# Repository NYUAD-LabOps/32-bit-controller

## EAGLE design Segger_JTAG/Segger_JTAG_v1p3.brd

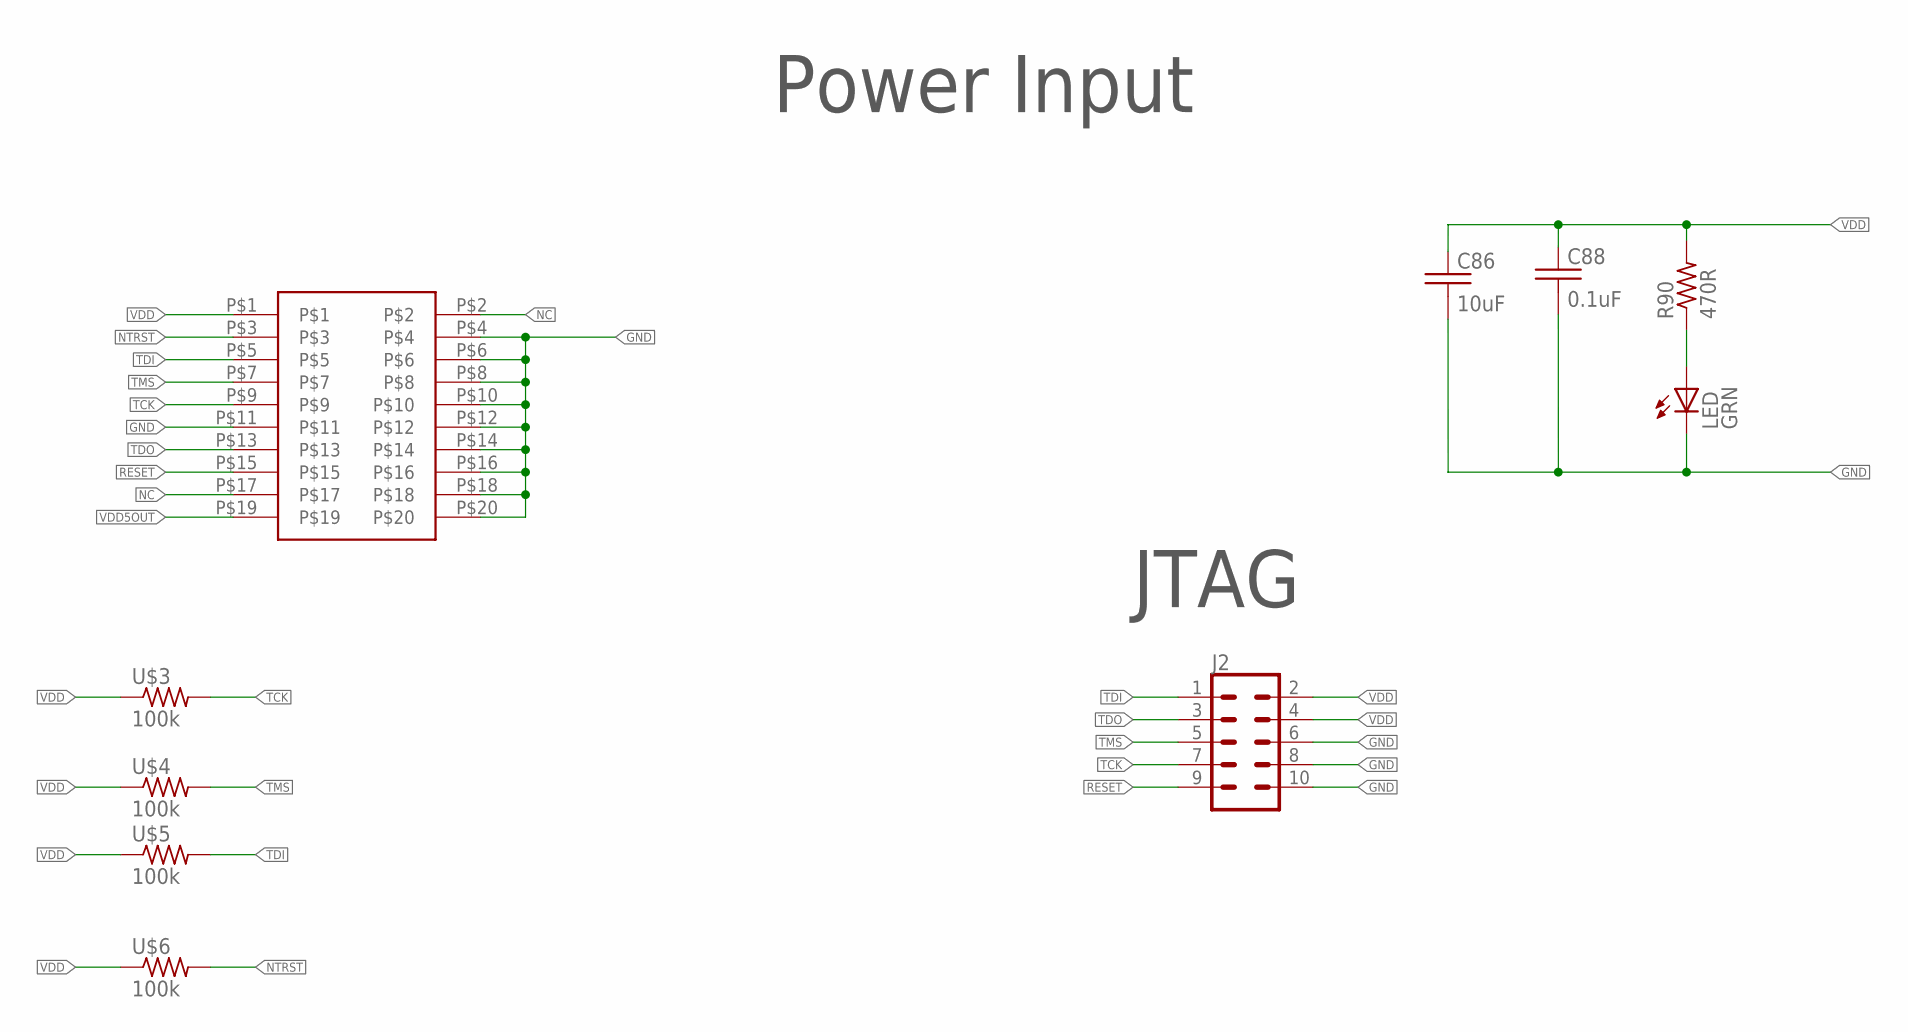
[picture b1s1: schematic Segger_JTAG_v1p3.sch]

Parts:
C86: 10uF; 0805
C88: 0.1uF; 0805
J2: CONN_05X2PTH; 2X5
LED: LED_0805_GREEN
R90: 470R; 0805
U$2: 2_X_10_HEADER_GENERIC; 2_X_10_.1_INCH
U$3, U$4, U$5, U$6: 100k; 0805

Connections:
GND: C86.2, C88.2, J2.6, J2.8, J2.10, LED.C, U$2.P$4, U$2.P$6, U$2.P$8, U$2.P$10, U$2.P$11, U$2.P$12, U$2.P$14, U$2.P$16, U$2.P$18, U$2.P$20
unnamed: LED.A, R90.1
NC: U$2.P$2, U$2.P$17
NTRST: U$2.P$3, U$6.2
RESET: J2.9, U$2.P$15
TCK: J2.7, U$2.P$9, U$3.2
TDI: J2.1, U$2.P$5, U$5.2
TDO: J2.3, U$2.P$13
TMS: J2.5, U$2.P$7, U$4.2
VDD: C86.1, C88.1, J2.2, J2.4, R90.2, U$2.P$1, U$3.1, U$4.1, U$5.1, U$6.1
VDD5OUT: U$2.P$19

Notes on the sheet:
Power Input
JTAG

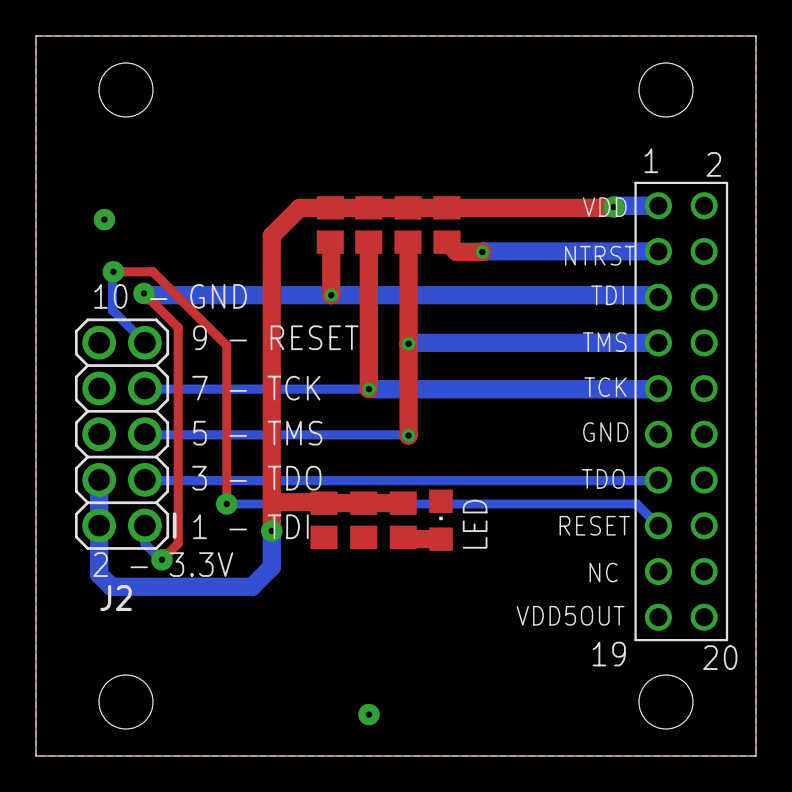
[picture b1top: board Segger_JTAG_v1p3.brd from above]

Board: 2 copper layers, 40.0 x 40.0 mm, 10 parts (0 on the bottom side), 10 nets.

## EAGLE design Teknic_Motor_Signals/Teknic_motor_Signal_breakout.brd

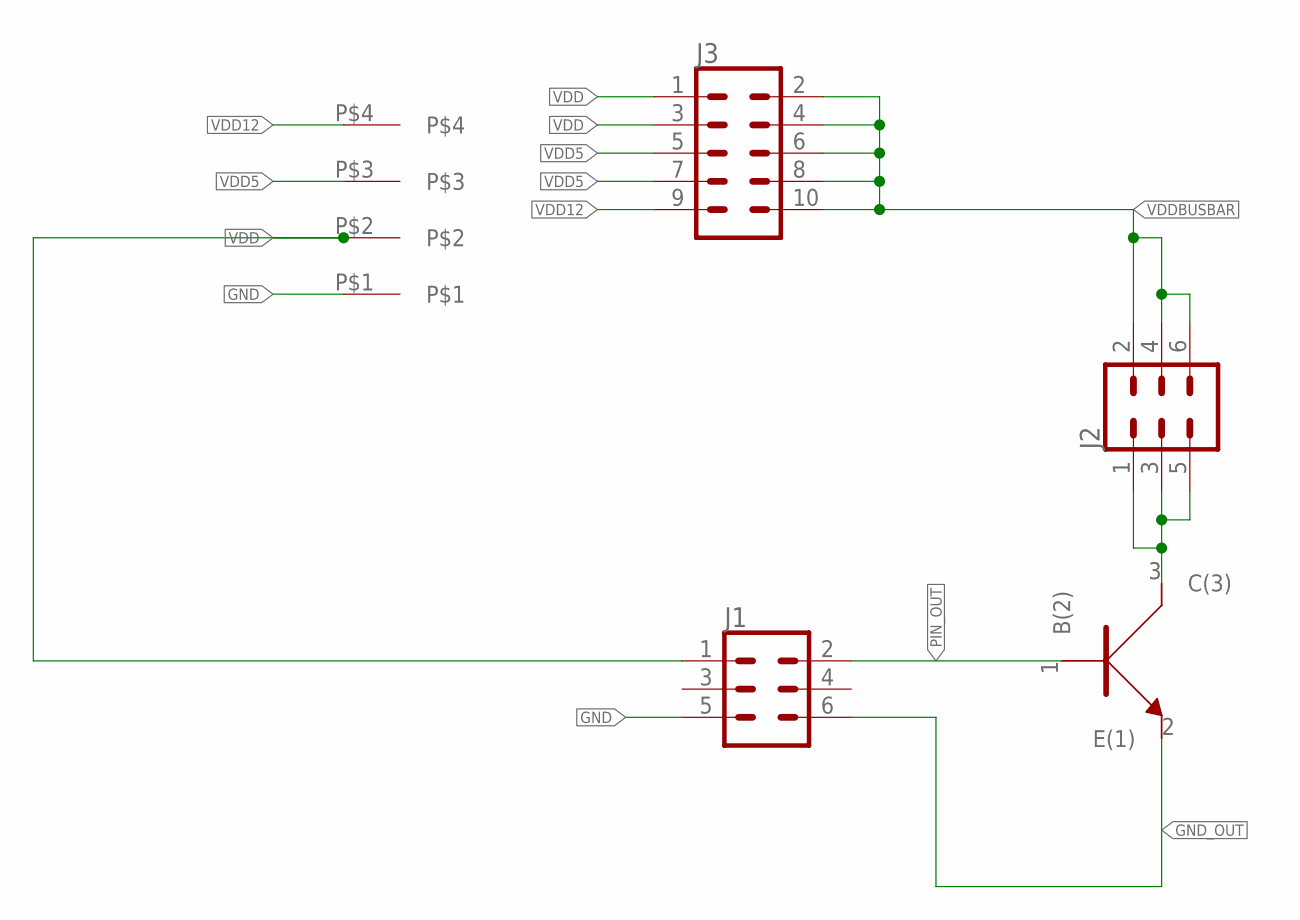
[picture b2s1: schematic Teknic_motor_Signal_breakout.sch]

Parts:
J1, J2: CONN_03X2; 2X3
J3: CONN_05X2PTH; 2X5
J5: 4-pos; 1X4_3.81MM_PITCH
U1: NPN; SOT323

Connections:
GND: J1.5, J5.P$1
GND_OUT: J1.6, U1.2 (E(1))
unnamed: J2.1, J2.3, J2.5, U1.3 (C(3))
PIN_OUT: J1.2, U1.1 (B(2))
VDD: J1.1, J3.1, J3.3, J5.P$2
VDD5: J3.5, J3.7, J5.P$3
VDD12: J3.9, J5.P$4
VDDBUSBAR: J2.2, J2.4, J2.6, J3.2, J3.4, J3.6, J3.8, J3.10

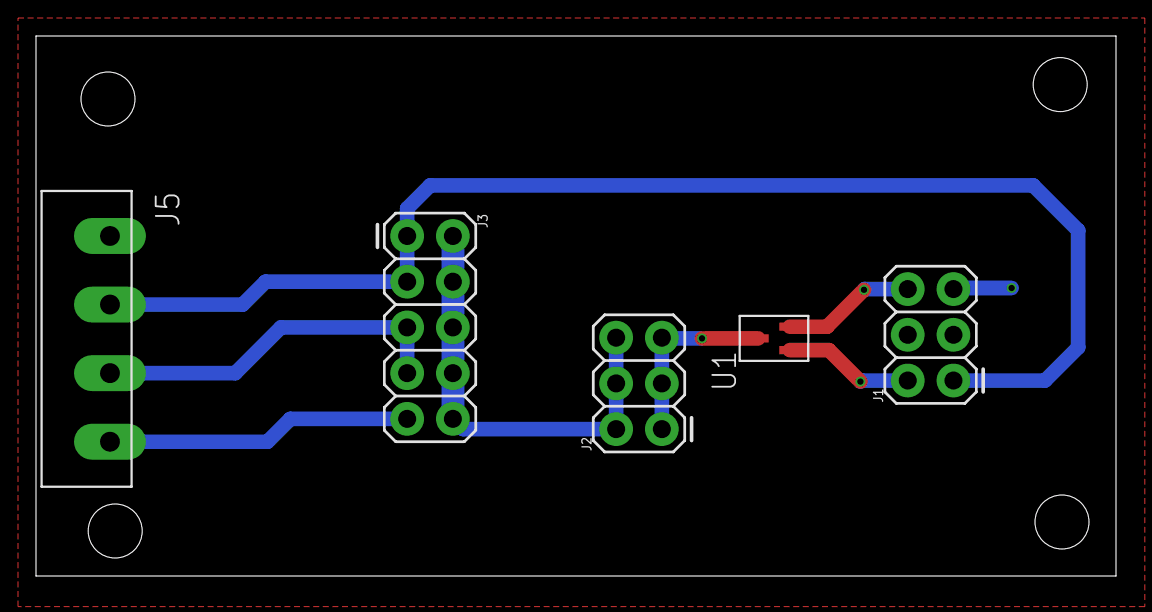
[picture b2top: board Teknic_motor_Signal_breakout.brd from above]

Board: 2 copper layers, 60.0 x 30.0 mm, 5 parts (0 on the bottom side), 8 nets.

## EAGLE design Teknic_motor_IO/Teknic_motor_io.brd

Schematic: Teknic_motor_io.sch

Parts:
J1, J2, J3, J4, J7, J9, J10, J11, J12: TEKNIC_8PIN_MOTOR; CON_39281083
J5: 2-pos; 2_3.81MM_PITCH
J8: 40-pos; HEADER_2_X_20_.1_INCH
R3, R7, R8, R10, R11, R21, R22, R24, R25, R29, R30, R32, R33, R37, R38, R40, R41, R45, R46, R48, R49, R53, R54, R56, R57, R61, R62, R64, R65, R69, R70, R72, R73, R77, R78, R80: 1K0; 0402
R4, R5, R6, R9, R12, R19, R20, R23, R26, R27, R28, R31, R34, R35, R36, R39, R42, R43, R44, R47, R50, R51, R52, R55, R58, R59, R60, R63, R66, R67, R68, R71, R74, R75, R76, R79: 33R0; 0402
U2, U3, U4, U5, U6, U10, U11, U12, U13, U14, U15, U16, U17, U18, U19, U20, U21, U22, U23, U24, U25, U26, U27, U28, U29, U30, U31, U32, U33, U34, U35, U36, U37, U38, U39, U40: NPN; SOT323

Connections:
GND: J5.P$1, J8.P$37, J8.P$38, J8.P$39, J8.P$40, U2.2 (E(1)), U3.2 (E(1)), U4.2 (E(1)), U5.2 (E(1)), U6.2 (E(1)), U10.2 (E(1)), U11.2 (E(1)), U12.2 (E(1)), U13.2 (E(1)), U14.2 (E(1)), U15.2 (E(1)), U16.2 (E(1)), U17.2 (E(1)), U18.2 (E(1)), U19.2 (E(1)), U20.2 (E(1)), U21.2 (E(1)), U22.2 (E(1)), U23.2 (E(1)), U24.2 (E(1)), U25.2 (E(1)), U26.2 (E(1)), U27.2 (E(1)), U28.2 (E(1)), U29.2 (E(1)), U30.2 (E(1)), U31.2 (E(1)), U32.2 (E(1)), U33.2 (E(1)), U34.2 (E(1)), U35.2 (E(1)), U36.2 (E(1)), U37.2 (E(1)), U38.2 (E(1)), U39.2 (E(1)), U40.2 (E(1))
M1_DIR: J8.P$2, R5.P$1 (1)
M1_ENABLE: J8.P$3, R6.P$1 (1)
M1_HLFB: R9.P$1 (1)
M1_STEP: J8.P$1, R4.P$1 (1)
M2_DIR: J8.P$5, R19.P$1 (1)
M2_ENABLE: J8.P$6, R20.P$1 (1)
M2_HLFB: R23.P$1 (1)
M2_STEP: J8.P$4, R12.P$1 (1)
M3_DIR: J8.P$8, R27.P$1 (1)
M3_ENABLE: J8.P$9, R28.P$1 (1)
M3_HLFB: R31.P$1 (1)
M3_STEP: J8.P$7, R26.P$1 (1)
M4_DIR: J8.P$11, R35.P$1 (1)
M4_ENABLE: J8.P$12, R36.P$1 (1)
M4_HLFB: R39.P$1 (1)
M4_STEP: J8.P$10, R34.P$1 (1)
M5_DIR: J8.P$14, R43.P$1 (1)
M5_ENABLE: J8.P$15, R44.P$1 (1)
M5_HLFB: R47.P$1 (1)
M5_STEP: J8.P$13, R42.P$1 (1)
M6_DIR: J8.P$17, R51.P$1 (1)
M6_ENABLE: J8.P$18, R52.P$1 (1)
M6_HLFB: R55.P$1 (1)
M6_STEP: J8.P$16, R50.P$1 (1)
M7_DIR: J8.P$20, R59.P$1 (1)
M7_ENABLE: J8.P$21, R60.P$1 (1)
M7_HLFB: R63.P$1 (1)
M7_STEP: J8.P$19, R58.P$1 (1)
M8_DIR: J8.P$23, R67.P$1 (1)
M8_ENABLE: J8.P$24, R68.P$1 (1)
M8_HLFB: R71.P$1 (1)
M8_STEP: J8.P$22, R66.P$1 (1)
M9_DIR: J8.P$26, R75.P$1 (1)
M9_ENABLE: J8.P$27, R76.P$1 (1)
M9_HLFB: R79.P$1 (1)
M9_STEP: J8.P$25, R74.P$1 (1)
M10_DIR: J8.P$29
M10_ENABLE: J8.P$30
M10_STEP: J8.P$28
M11_DIR: J8.P$32
M11_ENABLE: J8.P$33
M11_STEP: J8.P$31
M12_DIR: J8.P$35
M12_ENABLE: J8.P$36
M12_STEP: J8.P$34
MR_DIR: J1.7 (7-INPUT_A-), J2.7 (7-INPUT_A-), J3.7 (7-INPUT_A-), J4.7 (7-INPUT_A-), J7.7 (7-INPUT_A-), J9.7 (7-INPUT_A-), J10.7 (7-INPUT_A-), J11.7 (7-INPUT_A-), J12.7 (7-INPUT_A-), R7.P$1 (1), R21.P$1 (1), R29.P$1 (1), R37.P$1 (1), R45.P$1 (1), R53.P$1 (1), R61.P$1 (1), R69.P$1 (1), R77.P$1 (1), U3.3 (C(3)), U10.3 (C(3)), U14.3 (C(3)), U18.3 (C(3)), U22.3 (C(3)), U26.3 (C(3)), U30.3 (C(3)), U34.3 (C(3)), U38.3 (C(3))
MR_ENABLE: J1.8 (8-ENABLE-), J2.8 (8-ENABLE-), J3.8 (8-ENABLE-), J4.8 (8-ENABLE-), J7.8 (8-ENABLE-), J9.8 (8-ENABLE-), J10.8 (8-ENABLE-), J11.8 (8-ENABLE-), J12.8 (8-ENABLE-), R8.P$1 (1), R22.P$1 (1), R30.P$1 (1), R38.P$1 (1), R46.P$1 (1), R54.P$1 (1), R62.P$1 (1), R70.P$1 (1), R78.P$1 (1), U4.3 (C(3)), U11.3 (C(3)), U15.3 (C(3)), U19.3 (C(3)), U23.3 (C(3)), U27.3 (C(3)), U31.3 (C(3)), U35.3 (C(3)), U39.3 (C(3))
MR_HLFB: J1.5 (5-HLFB-), J2.5 (5-HLFB-), J3.5 (5-HLFB-), J4.5 (5-HLFB-), J7.5 (5-HLFB-), J9.5 (5-HLFB-), J10.5 (5-HLFB-), J11.5 (5-HLFB-), J12.5 (5-HLFB-), R10.P$1 (1), R24.P$1 (1), R32.P$1 (1), R40.P$1 (1), R48.P$1 (1), R56.P$1 (1), R64.P$1 (1), R72.P$1 (1), R80.P$1 (1), U5.3 (C(3)), U12.3 (C(3)), U16.3 (C(3)), U20.3 (C(3)), U24.3 (C(3)), U28.3 (C(3)), U32.3 (C(3)), U36.3 (C(3)), U40.3 (C(3))
MR_STEP: J1.6 (6-INPUT_B-), J2.6 (6-INPUT_B-), J3.6 (6-INPUT_B-), J4.6 (6-INPUT_B-), J7.6 (6-INPUT_B-), J9.6 (6-INPUT_B-), J10.6 (6-INPUT_B-), J11.6 (6-INPUT_B-), J12.6 (6-INPUT_B-), R3.P$1 (1), R11.P$1 (1), R25.P$1 (1), R33.P$1 (1), R41.P$1 (1), R49.P$1 (1), R57.P$1 (1), R65.P$1 (1), R73.P$1 (1), U2.3 (C(3)), U6.3 (C(3)), U13.3 (C(3)), U17.3 (C(3)), U21.3 (C(3)), U25.3 (C(3)), U29.3 (C(3)), U33.3 (C(3)), U37.3 (C(3))
unnamed: R5.P$2 (2), U3.1 (B(2))
unnamed: R6.P$2 (2), U4.1 (B(2))
unnamed: R4.P$2 (2), U2.1 (B(2))
unnamed: R9.P$2 (2), U5.1 (B(2))
unnamed: R19.P$2 (2), U10.1 (B(2))
unnamed: R20.P$2 (2), U11.1 (B(2))
unnamed: R12.P$2 (2), U6.1 (B(2))
unnamed: R23.P$2 (2), U12.1 (B(2))
unnamed: R27.P$2 (2), U14.1 (B(2))
unnamed: R28.P$2 (2), U15.1 (B(2))
unnamed: R26.P$2 (2), U13.1 (B(2))
unnamed: R31.P$2 (2), U16.1 (B(2))
unnamed: R35.P$2 (2), U18.1 (B(2))
unnamed: R36.P$2 (2), U19.1 (B(2))
unnamed: R34.P$2 (2), U17.1 (B(2))
unnamed: R39.P$2 (2), U20.1 (B(2))
unnamed: R43.P$2 (2), U22.1 (B(2))
unnamed: R44.P$2 (2), U23.1 (B(2))
unnamed: R42.P$2 (2), U21.1 (B(2))
unnamed: R47.P$2 (2), U24.1 (B(2))
unnamed: R51.P$2 (2), U26.1 (B(2))
unnamed: R52.P$2 (2), U27.1 (B(2))
unnamed: R50.P$2 (2), U25.1 (B(2))
unnamed: R55.P$2 (2), U28.1 (B(2))
unnamed: R59.P$2 (2), U30.1 (B(2))
unnamed: R60.P$2 (2), U31.1 (B(2))
unnamed: R58.P$2 (2), U29.1 (B(2))
unnamed: R63.P$2 (2), U32.1 (B(2))
unnamed: R67.P$2 (2), U34.1 (B(2))
unnamed: R68.P$2 (2), U35.1 (B(2))
unnamed: R66.P$2 (2), U33.1 (B(2))
unnamed: R71.P$2 (2), U36.1 (B(2))
unnamed: R75.P$2 (2), U38.1 (B(2))
unnamed: R76.P$2 (2), U39.1 (B(2))
unnamed: R74.P$2 (2), U37.1 (B(2))
unnamed: R79.P$2 (2), U40.1 (B(2))
VDD12: J1.1 (1-HLFB+), J1.2 (2-INPUT_B+), J1.3 (3-INPUT_A+), J1.4 (4-ENABLE+), J2.1 (1-HLFB+), J2.2 (2-INPUT_B+), J2.3 (3-INPUT_A+), J2.4 (4-ENABLE+), J3.1 (1-HLFB+), J3.2 (2-INPUT_B+), J3.3 (3-INPUT_A+), J3.4 (4-ENABLE+), J4.1 (1-HLFB+), J4.2 (2-INPUT_B+), J4.3 (3-INPUT_A+), J4.4 (4-ENABLE+), J5.P$2, J7.1 (1-HLFB+), J7.2 (2-INPUT_B+), J7.3 (3-INPUT_A+), J7.4 (4-ENABLE+), J9.1 (1-HLFB+), J9.2 (2-INPUT_B+), J9.3 (3-INPUT_A+), J9.4 (4-ENABLE+), J10.1 (1-HLFB+), J10.2 (2-INPUT_B+), J10.3 (3-INPUT_A+), J10.4 (4-ENABLE+), J11.1 (1-HLFB+), J11.2 (2-INPUT_B+), J11.3 (3-INPUT_A+), J11.4 (4-ENABLE+), J12.1 (1-HLFB+), J12.2 (2-INPUT_B+), J12.3 (3-INPUT_A+), J12.4 (4-ENABLE+), R3.P$2 (2), R7.P$2 (2), R8.P$2 (2), R10.P$2 (2), R11.P$2 (2), R21.P$2 (2), R22.P$2 (2), R24.P$2 (2), R25.P$2 (2), R29.P$2 (2), R30.P$2 (2), R32.P$2 (2), R33.P$2 (2), R37.P$2 (2), R38.P$2 (2), R40.P$2 (2), R41.P$2 (2), R45.P$2 (2), R46.P$2 (2), R48.P$2 (2), R49.P$2 (2), R53.P$2 (2), R54.P$2 (2), R56.P$2 (2), R57.P$2 (2), R61.P$2 (2), R62.P$2 (2), R64.P$2 (2), R65.P$2 (2), R69.P$2 (2), R70.P$2 (2), R72.P$2 (2), R73.P$2 (2), R77.P$2 (2), R78.P$2 (2), R80.P$2 (2)

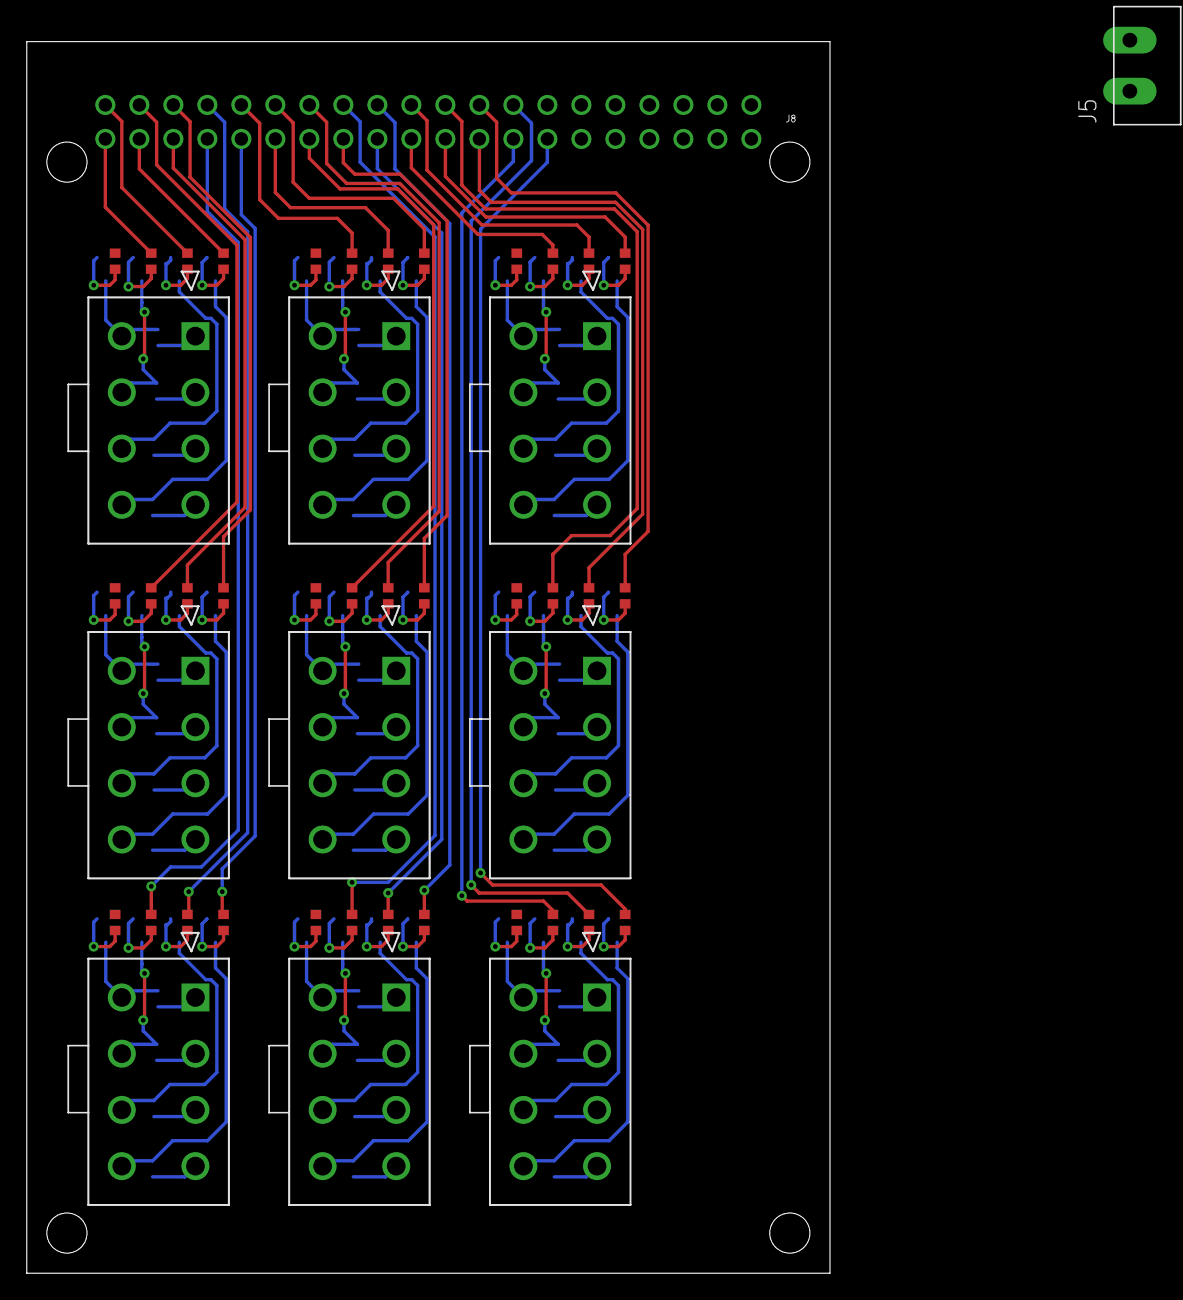
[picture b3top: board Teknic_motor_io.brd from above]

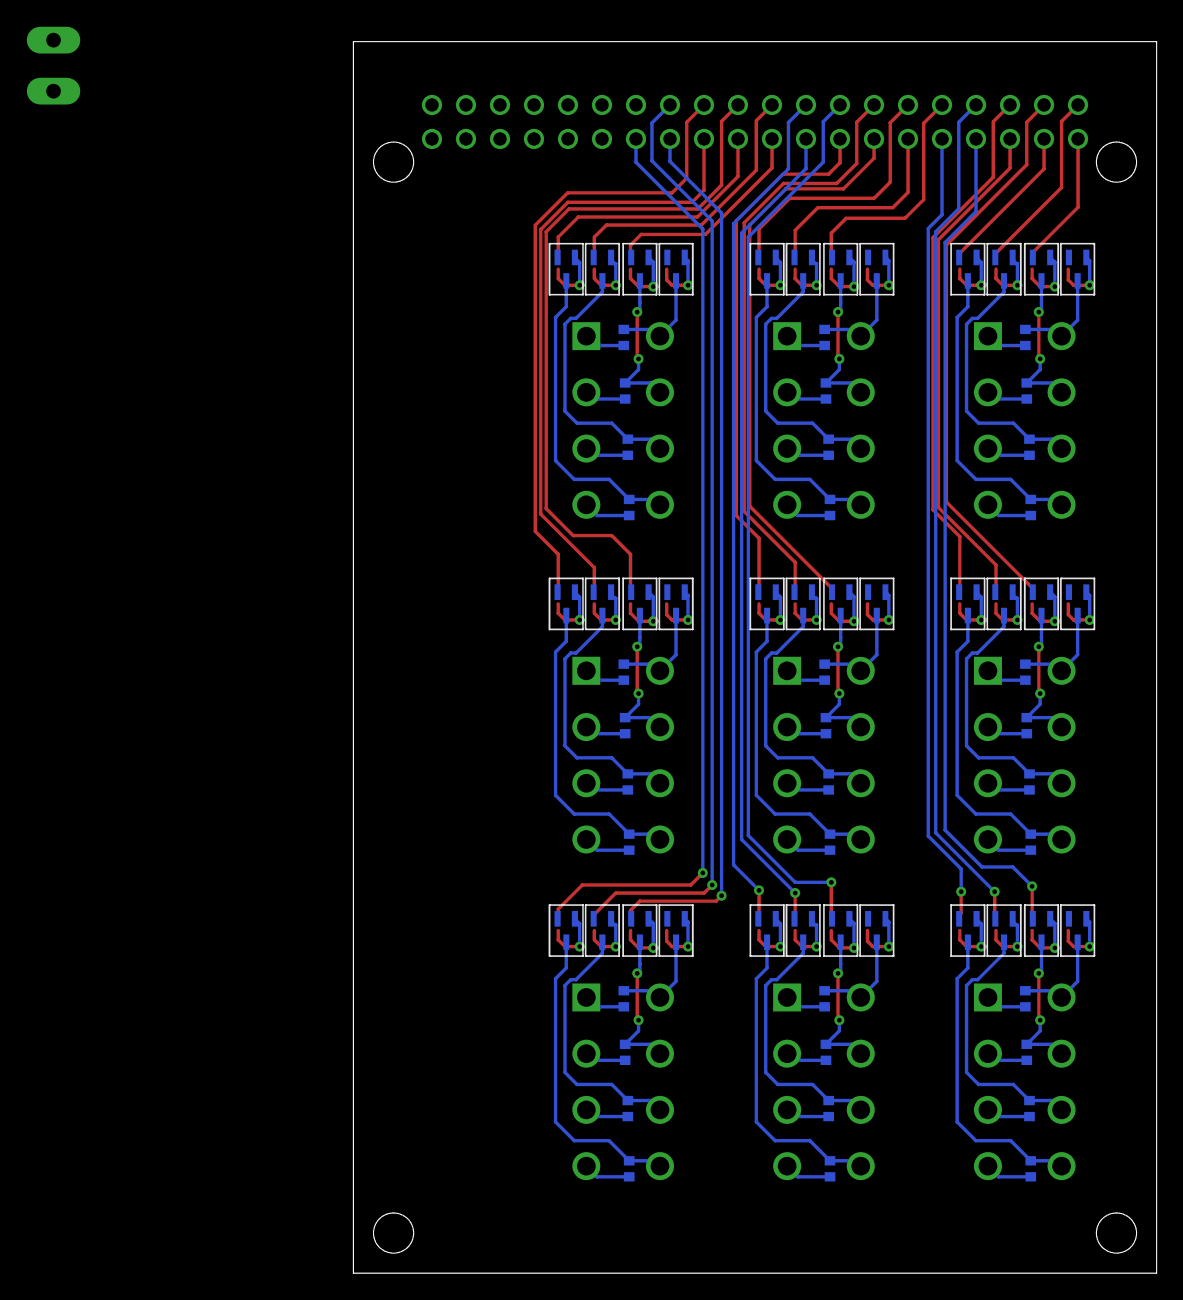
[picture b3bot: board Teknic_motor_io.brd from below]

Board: 2 copper layers, 60.0 x 92.0 mm, 119 parts (72 on the bottom side), 69 nets.

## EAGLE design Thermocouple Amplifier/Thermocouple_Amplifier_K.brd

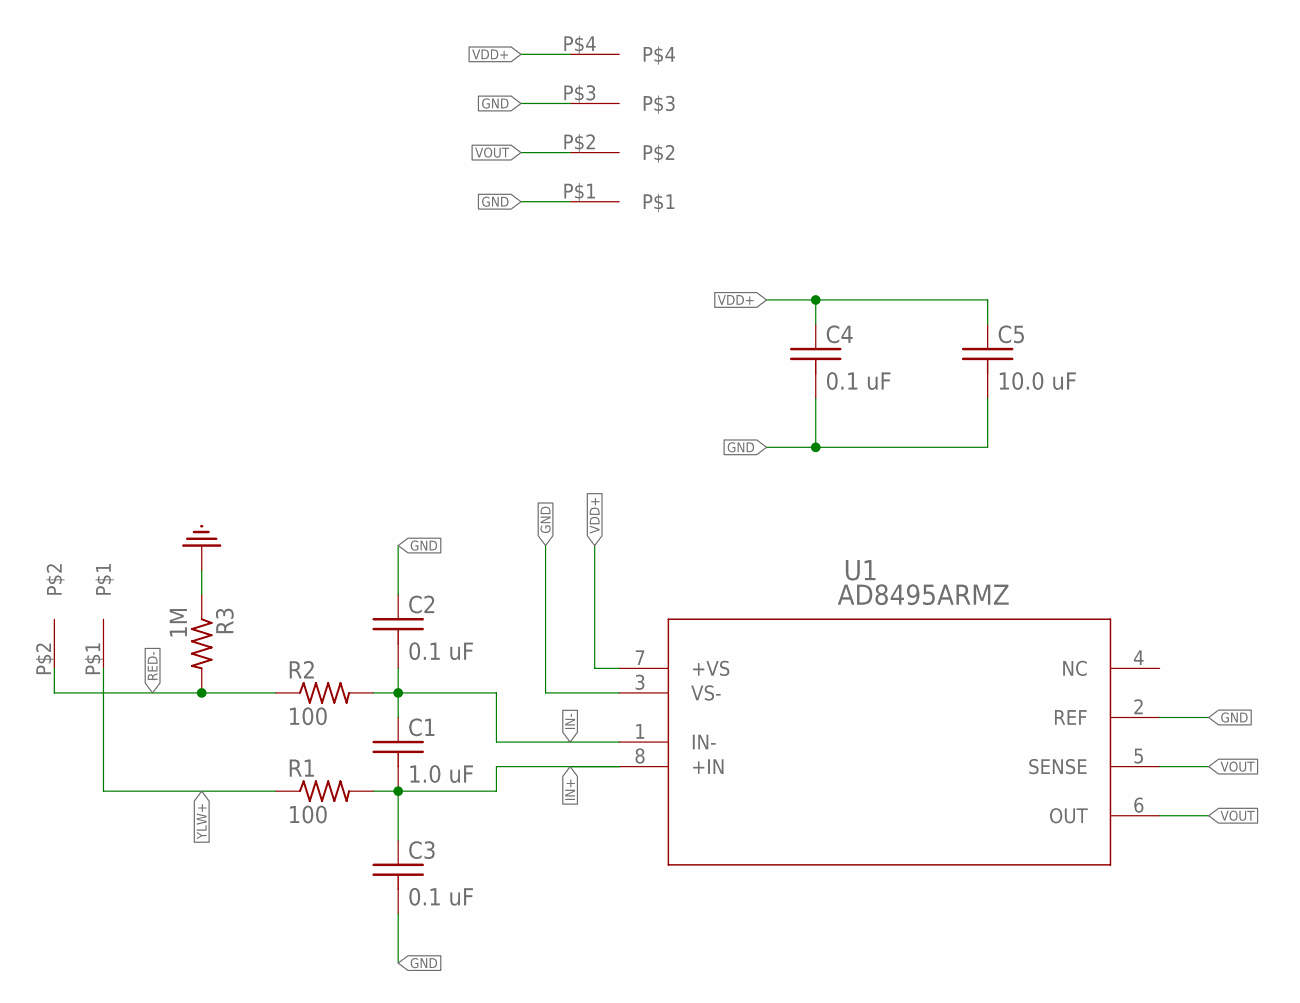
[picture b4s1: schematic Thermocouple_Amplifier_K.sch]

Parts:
C1: 1.0 uF; 0402
C2, C3, C4: 0.1 uF; 0402
C5: 10.0 uF; 0402
J1: 3.81MM_1_X_2_RT_ANGLE_PLUG_HEADER; 2_3.81MM_PITCH
J2: 3.81MM_1_X_4_RT_ANGLE_PLUG_HEADER; 1X4_3.81MM_PITCH
R1, R2: 100; 0402
R3: 1M; 0402
U1: AD8495ARMZ; RM_8_ADI

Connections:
GND: C2.P$1 (1), C3.P$2 (2), C4.P$2 (2), C5.P$2 (2), J2.P$1, J2.P$3, R3.P$1 (1), U1.2 (REF), U1.3 (VS-)
IN+: C1.P$2 (2), C3.P$1 (1), R1.P$2 (2), U1.8 (+IN)
IN-: C1.P$1 (1), C2.P$2 (2), R2.P$2 (2), U1.1 (IN-)
RED-: J1.P$2, R2.P$1 (1), R3.P$2 (2)
VDD+: C4.P$1 (1), C5.P$1 (1), J2.P$4, U1.7 (+VS)
VOUT: J2.P$2, U1.5 (SENSE), U1.6 (OUT)
YLW+: J1.P$1, R1.P$1 (1)

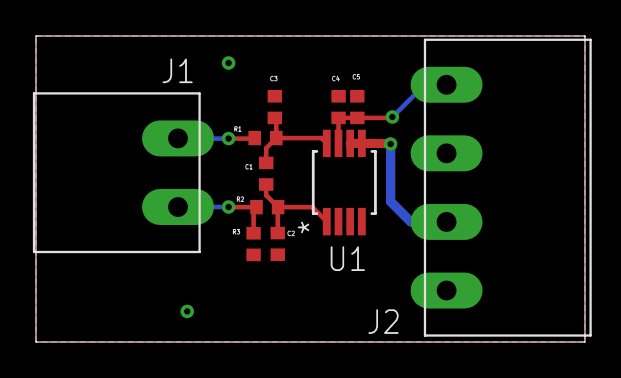
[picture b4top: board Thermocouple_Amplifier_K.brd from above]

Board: 2 copper layers, 30.5 x 17.0 mm, 11 parts (0 on the bottom side), 7 nets.

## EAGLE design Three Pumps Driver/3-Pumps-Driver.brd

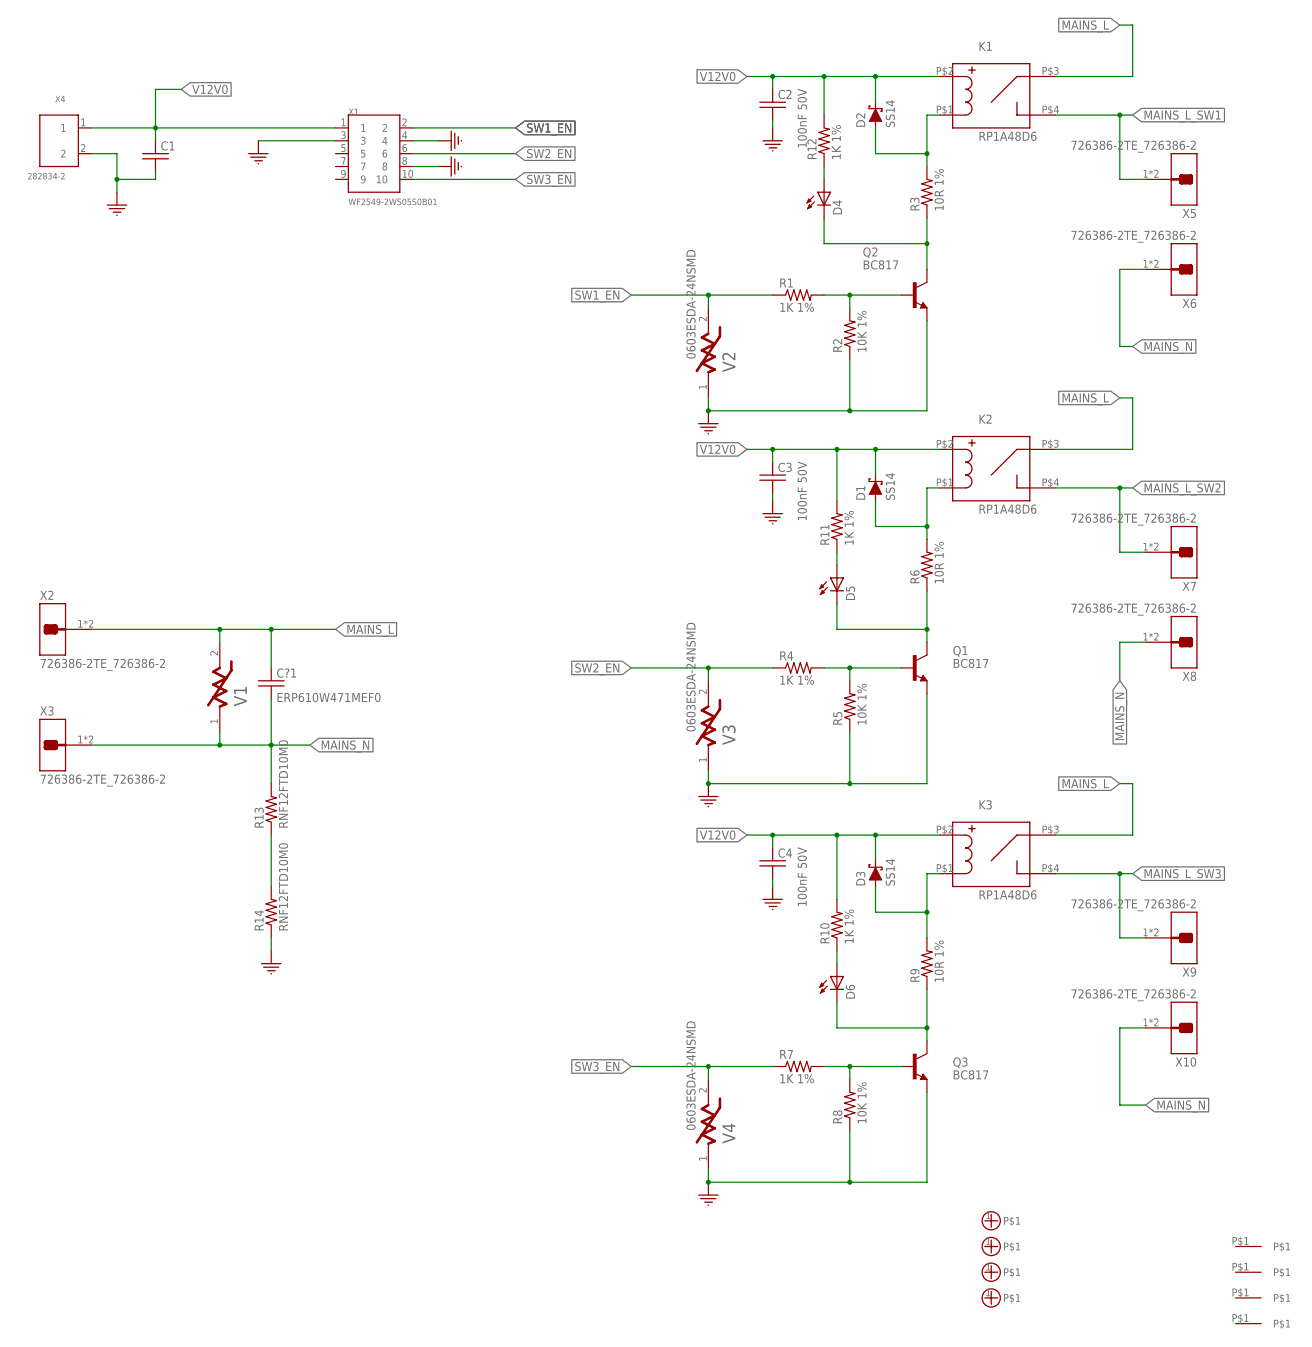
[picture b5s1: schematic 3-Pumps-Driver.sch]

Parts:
C1: C_0603EIA0603; EIA0603
C2, C3, C4: 100nF 50V; EIA0603
C?1: ERP610W471MEF0; CAPACITOR-FILM-RM12.5MM-12MM
D1, D2, D3: SS14; SMA
D4, D5, D6: 26-21/GPC-F3138B/CA; SMD1206-LED
FID1, FID2, FID3, FID4: FIDUCIAL
K1, K2, K3: RP1A48D6; SSR_RP1A
M1, M2, M3, M4: M_HOLE_3M; PCB_SCREW_M3_POWER
Q1, Q2, Q3: BC817; SOT23
R1, R4, R7: 1K 1%; EIA0603
R2, R5, R8: 10K 1%; EIA0603
R3, R6, R9: 10R 1%; EIA1206
R10, R11, R12: 1K 1%; EIA1206
R13, R14: RNF12FTD10M0; RES-RM12.5-VR37
V1: B72205S0271K101B72205S2131K101; EPCOS_B72205S0271K101_0
V2, V3, V4: 0603ESDA-24NSMD; EIA0603
X1: WF2549-2WS05S0B01; X10_100MIL_2XROW_VERT
X2, X3, X5, X6, X7, X8, X9, X10: 726386-2TE_726386-2; TE_726386-2
X4: 282834-2; TE_282834-2_0

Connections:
GND: C1.2, C2.2, C3.2, C4.2, Q1.2 (E), Q2.2 (E), Q3.2 (E), R2.1, R5.1, R8.1, R14.1, V2.1, V3.1, V4.1, X1.3, X1.4, X1.8, X4.2
MAINS_L: C?1.1, K1.P$3 (3), K2.P$3 (3), K3.P$3 (3), V1.2, X2.1, X2.1-2
MAINS_L_SW1: K1.P$4 (4), X5.1, X5.1-2
MAINS_L_SW2: K2.P$4 (4), X7.1, X7.1-2
MAINS_L_SW3: K3.P$4 (4), X9.1, X9.1-2
MAINS_N: C?1.2, R13.2, V1.1, X3.1, X3.1-2, X6.1, X6.1-2, X8.1, X8.1-2, X10.1, X10.1-2
unnamed: D4.1 (A), R12.1
unnamed: Q2.1 (B), R1.2, R2.2
unnamed: Q1.1 (B), R4.2, R5.2
unnamed: D2.2 (A), K1.P$1 (1), R3.2
unnamed: D1.2 (A), K2.P$1 (1), R6.2
unnamed: D5.1 (A), R11.1
unnamed: D4.2 (C), Q2.3 (C), R3.1
unnamed: D5.2 (C), Q1.3 (C), R6.1
unnamed: Q3.1 (B), R7.2, R8.2
unnamed: D3.2 (A), K3.P$1 (1), R9.2
unnamed: D6.1 (A), R10.1
unnamed: R13.1, R14.2
unnamed: D6.2 (C), Q3.3 (C), R9.1
SW1_EN: R1.1, V2.2, X1.2
SW2_EN: R4.1, V3.2, X1.6
SW3_EN: R7.1, V4.2, X1.10
V12V0: C1.1, C2.1, C3.1, C4.1, D1.1 (C), D2.1 (C), D3.1 (C), K1.P$2 (2), K2.P$2 (2), K3.P$2 (2), R10.2, R11.2, R12.2, X1.1, X4.1

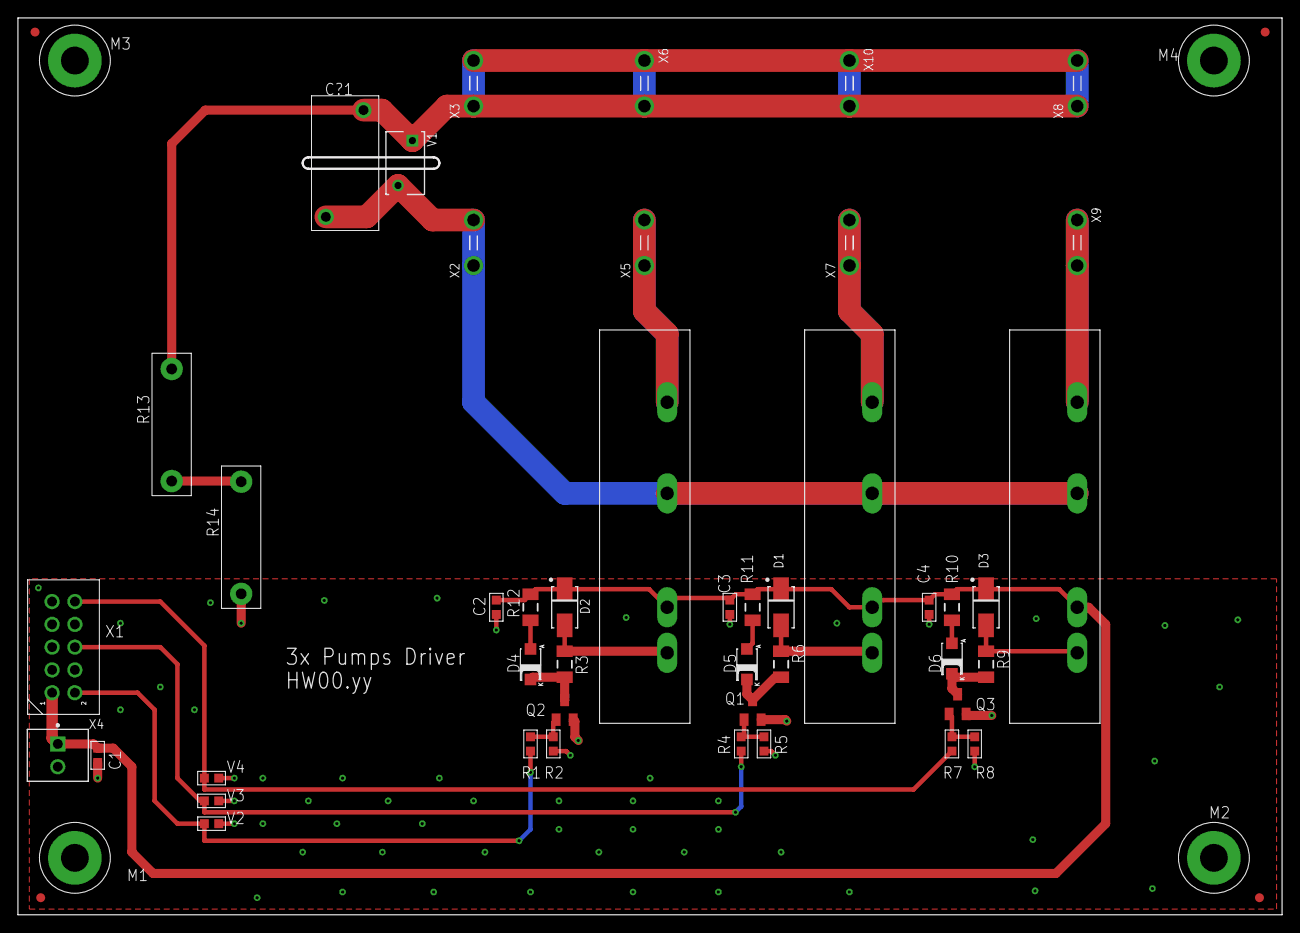
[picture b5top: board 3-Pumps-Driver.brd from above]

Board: 2 copper layers, 140.9 x 100.0 mm, 53 parts (0 on the bottom side), 23 nets.

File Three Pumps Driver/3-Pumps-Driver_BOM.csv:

"Qty";"Value";"Device";"Package";"Parts";"Description";"CENTROID_NOT_SPECIFIED";"CONN_GENDER";"CONN_ORIENTATION";"CONTACT_MATERIAL";"DATASHEET";"DESCRIPTION";"DEVICE_CLASS_L1";"DEVICE_CLASS_L2";"DEVICE_CLASS_L3";"DIGIKEY_DESCRIPTION";"DIGIKEY_PART_NUMBER";"HEIGHT";"LEAD_FREE";"LIB_STATUS";"MF";"MFG_PACKAGE_IDENT";"MFG_PACKAGE_IDENT_DATE";"MFG_PACKAGE_IDENT_REV";"MFN";"MFR";"MOUSER_DESCRIPTION";"MOUSER_PART_NUMBER";"MPN";"OUR-STOCK";"OUR_STOCK";"PACKAGE";"PART_VALUE";"PREFIX";"PRICE-1";"ROHS";"SUPPLIER-1";"TEMPERATURE_RANGE_HIGH";"TEMPERATURE_RANGE_LOW";"VERIFICATION_VERSION";
"1";"";"C_0603EIA0603";"EIA0603";"C1";"";"";"";"";"";"";"";"";"";"";"";"";"";"";"";"";"";"";"";"";"";"";"";"";"";"";"";"";"";"";"";"";"";"";"";
"3";"0603ESDA-24NSMD";"0603ESDA-24NSMD";"EIA0603";"V2, V3, V4";"";"";"";"";"";"";"aristor 0603 SMD Bidirectional 50V 24V";"";"";"";"";"";"";"";"";"";"";"";"";"0603ESDA-24N";"Bourns";"";"";"";"";"";"";"";"";"";"";"LCSC";"";"";"";
"3";"100nF 50V";"C_0603EIA0603";"EIA0603";"C2, C3, C4";"";"";"";"";"";"";"";"";"";"";"";"";"";"";"";"";"";"";"";"";"";"";"";"";"";"";"";"";"";"";"";"";"";"";"";
"3";"10K 1%";"R_0603";"EIA0603";"R2, R5, R8";"";"";"";"";"";"";"";"";"";"";"";"";"";"";"";"";"";"";"";"Open Source 0603";"";"";"";"";"";"";"";"";"";"";"";"";"";"";"";
"3";"10R 1%";"R_1206EIA1206";"EIA1206";"R3, R6, R9";"";"";"";"";"";"";"";"";"";"";"";"";"";"";"";"";"";"";"";"Open Source R1206";"";"";"";"";"";"";"";"";"";"";"";"";"";"";"";
"3";"1K 1%";"R_0603";"EIA0603";"R1, R4, R7";"";"";"";"";"";"";"";"";"";"";"";"";"";"";"";"";"";"";"";"Open Source 0603";"";"";"";"";"";"";"";"";"";"";"";"";"";"";"";
"3";"1K 1%";"R_1206EIA1206";"EIA1206";"R10, R11, R12";"";"";"";"";"";"";"";"";"";"";"";"";"";"";"";"";"";"";"";"Open Source R1206";"";"";"";"";"";"";"";"";"";"";"";"";"";"";"";
"3";"26-21/GPC-F3138B/CA";"26-21/GPC-F3138B/CA";"SMD1206-LED";"D4, D5, D6";"";"";"";"";"";"";"Green SMD LED 1206, 160mcd";"";"";"";"";"";"";"";"Prototype";"";"";"";"";"26-21/GPC-F3138B/CA";"Everlight";"";"";"";"";"50";"";"Green LED";"";"0.06";"";"LCSC";"";"";"";
"1";"282834-2";"282834-2";"TE_282834-2_0";"X4";"";"";"";"";"";"";"Connector Header Terminal Block 2 Positions, 1 Row, 2.54mm, THT";"";"";"";"";"";"";"";"";"";"";"";"";"282834-2";"TE";"";"";"";"";"";"";"";"";"0.8";"";"Digikey";"";"";"";
"8";"726386-2TE_726386-2";"726386-2TE_726386-2";"TE_726386-2";"X2, X3, X5, X6, X7, X8, X9, X10";"Terminals, Faston, GDS-Flachstecker 6.3x0.8mm, TE";"No";"Male";"Straight";"Tin";"http://www.te.com/commerce/DocumentDelivery/DDEController?Ac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";"";"Connectors";"Terminal Blocks | Terminals";"unset";"CONN QC TAB 0.250 SOLDER";"A114371-ND";"10mm";"yes";"";"TE";"726386-2";"0";"0";"";"";"Terminals GDS-FLACHSTECK 6.3";"571-726386-2";"726386-2";"";"";"PTH_TERMINAL_8MM0_0MM8";"";"J";"";"yes";"";"+110°C";"-30°C";"0.0.0.1";
"1";"B72205S0271K101B72205S2131K101";"B72205S0271K101B72205S2131K101";"EPCOS_B72205S0271K101_0";"V1";"VARISTOR 205V 800A DISC 5MM";"";"";"";"";"";"";"";"";"";"";"";"";"";"Verified";"";"";"";"";"B72205S0271K1011";"EPCOS";"";"";"";"";"10";"";"430V, 400A";"";"0.31";"";"Digikey";"";"";"";
"3";"BC817";"BC817";"SOT23";"Q1, Q2, Q3";"";"";"";"";"";"";"Transistor BJT NPN SOT23 45V 0.5A";"";"";"";"";"";"";"";"";"";"";"";"";"BC817";"NXP";"";"";"";"";"";"";"";"";"0.03";"";"Mouser";"";"";"";
"1";"ERP610W471MEF0";"ERP610W471MEF0";"CAPACITOR-FILM-RM12.5MM-12MM";"C?1";"";"";"";"";"";"";"470pF ±20% 760V Ceramic Capacitor Radial, Y5U, X1,Y1";"";"";"";"";"";"";"";"";"";"";"";"";"ERP610W471MEF0";"Vishay";"";"";"";"";"";"";"470pF/760V";"";"";"";"";"";"";"";
"4";"FIDUCIAL";"FIDUCIAL";"FIDUCIAL";"FID1, FID2, FID3, FID4";"";"";"";"";"";"";"";"";"";"";"";"";"";"";"";"";"";"";"";"";"";"";"";"";"";"";"";"";"";"";"";"";"";"";"";
"4";"M_HOLE_3M";"M_HOLE_3M";"PCB_SCREW_M3_POWER";"M1, M2, M3, M4";"";"";"";"";"";"";"";"";"";"";"";"";"";"";"";"";"";"";"";"";"";"";"";"";"";"";"";"";"";"";"";"";"";"";"";
"2";"RNF12FTD10M0";"RNF12FTD10M0";"RES-RM12.5-VR37";"R13, R14";"";"";"";"";"";"";"10 MOhms ±1% 0.5W, 1/2W Through Hole Resistor Axial Flame Retardant Coating, Safety Metal Film";"";"";"";"";"";"";"";"Prototype";"";"";"";"";"RNF12FTD10M0";"Stackpole Electronics Inc";"";"";"";"20";"";"";"10Meg 5%";"";"0.29";"";"Digikey";"";"";"";
"3";"RP1A48D6";"RP1A48D6";"SSR_RP1A";"K1, K2, K3";"";"";"";"";"";"";"";"";"";"";"";"";"";"";"";"";"";"";"";"";"";"";"";"";"";"";"";"";"";"";"";"";"";"";"";
"3";"SS14";"SS14";"SMA";"D1, D2, D3";"";"";"";"";"";"";"Diode Schottky 1A/40V (SMA)";"";"";"";"";"";"";"";"Prototype";"";"";"";"";"SS14-LTP";"MCC";"";"";"";"";"10";"";"Schottky 1A/40V";"";"0.05";"";"LCSC";"";"";"";
"1";"WF2549-2WS05S0B01";"WF2549-2WS05S0B01";"X10_100MIL_2XROW_VERT";"X1";"";"";"";"";"";"";"X10, 10 Pins, Header, Pitch 2.54 wire to board 2xrows, THT";"";"";"";"";"";"";"";"";"";"";"";"";"WF2549-2WS05S0B01";"WCON";"";"";"";"";"";"";"";"";"0.25";"";"LCSC";"";"";"";

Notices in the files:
parts and their libraries:
COPYRIGHT: Copyright (C) 2022 Ultra Librarian. All rights reserved.
COPYRIGHT: Copyright (C) 2018 Accelerated Designs. All rights reserved
